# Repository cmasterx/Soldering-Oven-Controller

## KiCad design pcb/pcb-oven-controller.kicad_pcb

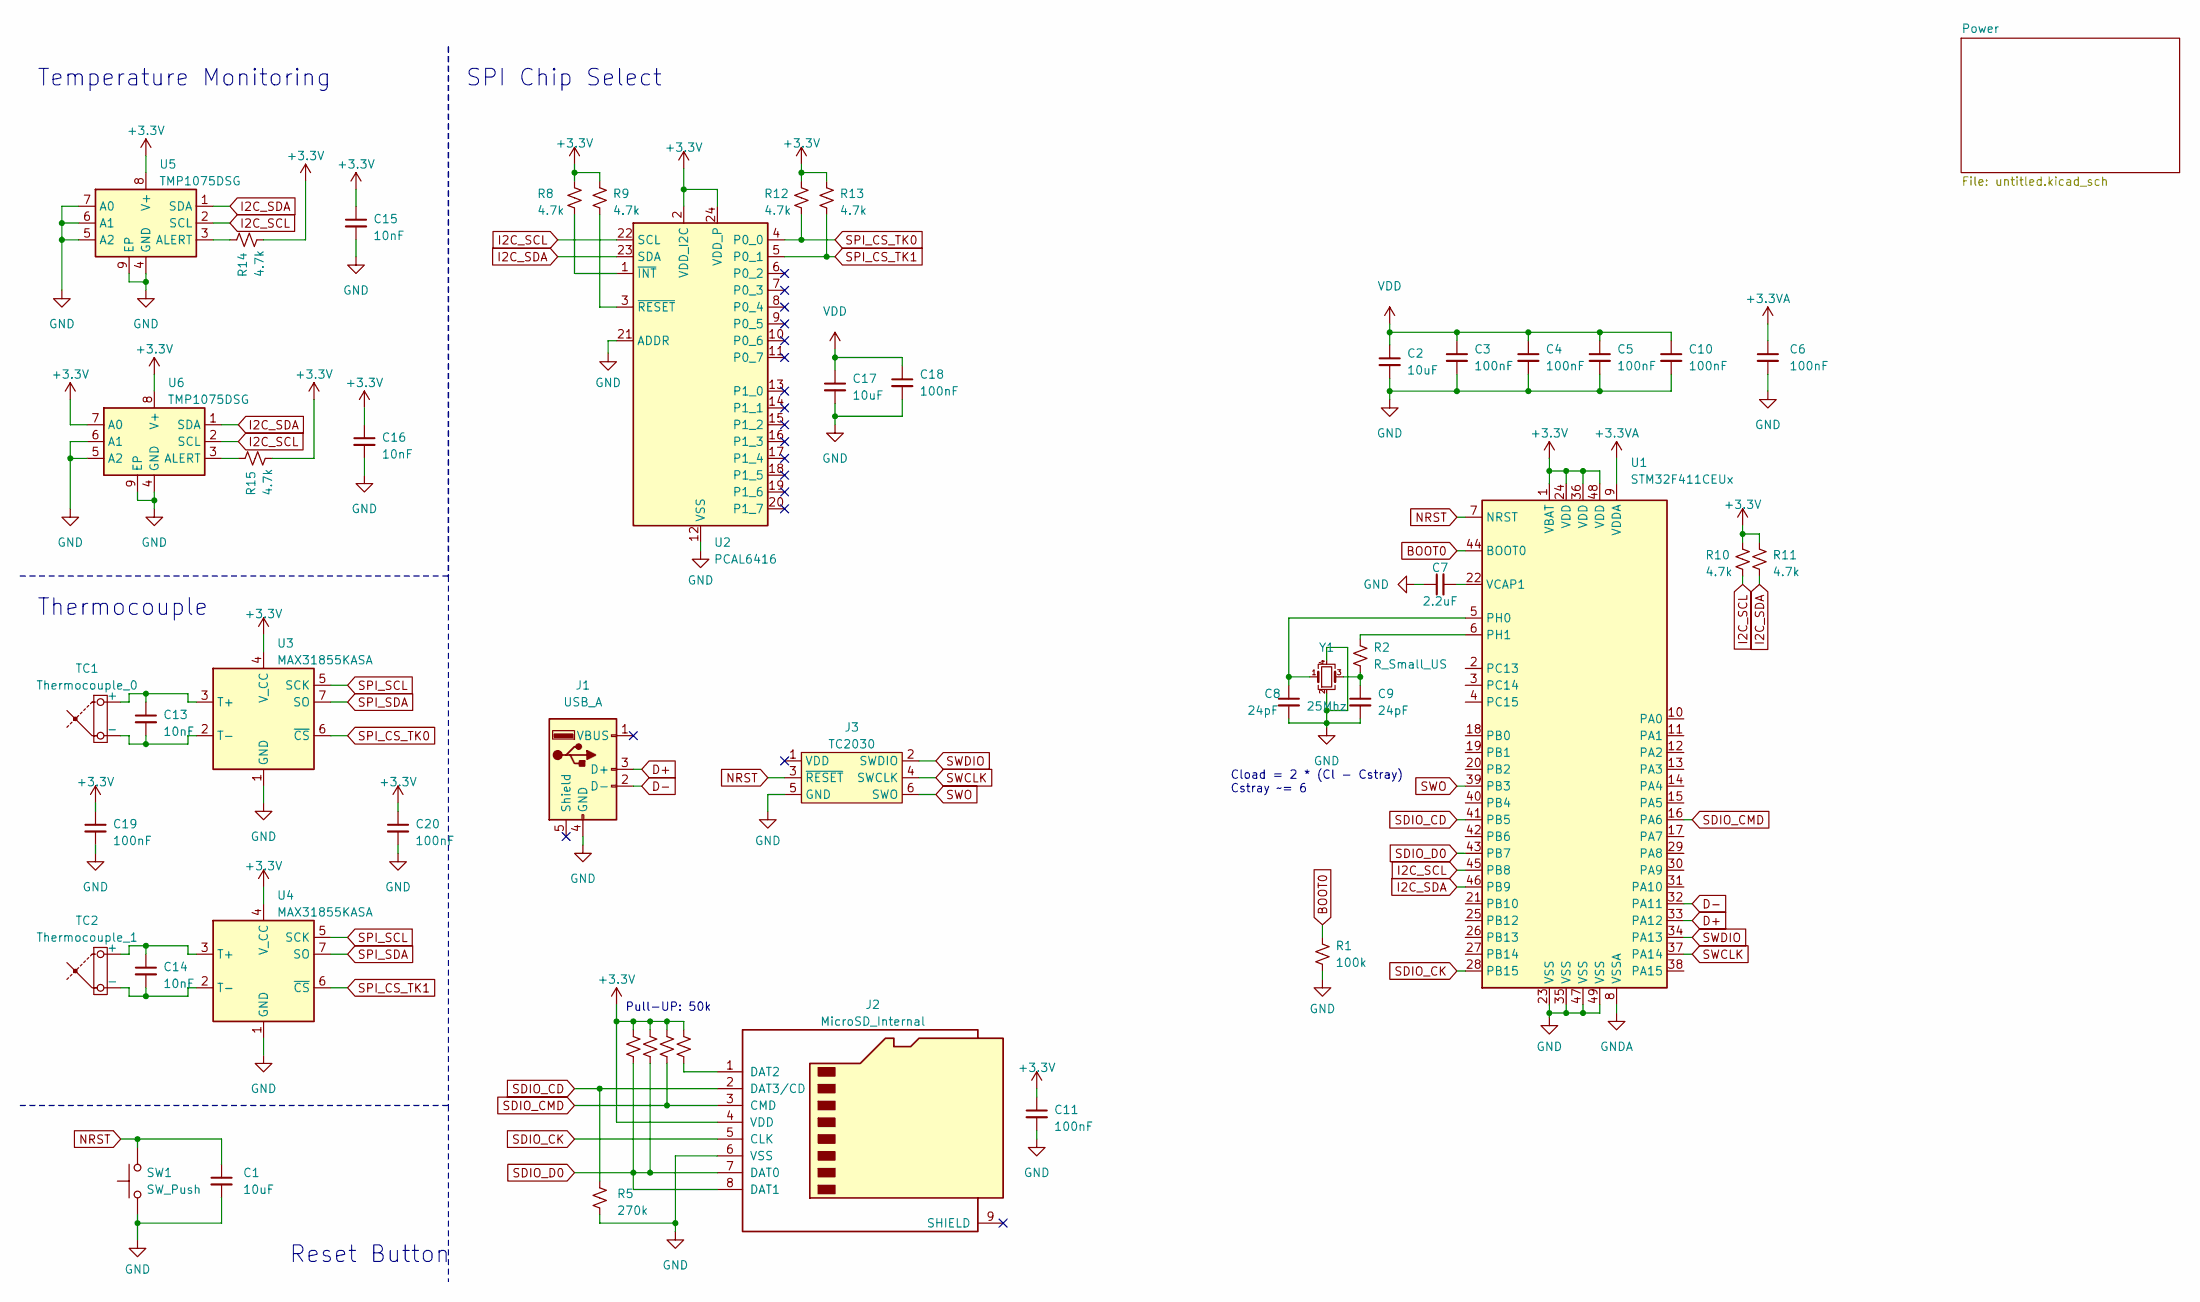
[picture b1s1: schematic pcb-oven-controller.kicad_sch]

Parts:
C1, C2, C17: 10uF; C_0603_1608Metric
C3, C4, C5, C6, C10, C18: 100nF; C_0402_1005Metric
C7: 2.2uF; C_0805_2012Metric
C8, C9: 24pF; C_0402_1005Metric
C11, C19, C20: 100nF; C_0603_1608Metric
C13, C14, C15, C16: 10nF; C_0603_1608Metric
J1: USB_A; USB_A_CNCTech_1001-011-01101_Horizontal
J2: MicroSD_Internal
J3: TC2030; Tag-Connect_TC2030-IDC-NL_2x03_P1.27mm_Vertical
R1: 100k; R_0402_1005Metric
R2: R_Small_US; R_0402_1005Metric
R3, R4, R6, R7: 50k; R_0603_1608Metric
R5: 270k; R_0603_1608Metric
R8, R9, R10, R14, R15: 4.7k; R_0603_1608Metric
R11, R12, R13: 4.7k; R_0603_1608Metric_Pad0.98x0.95mm_HandSolder
SW1: SW_Push; SW_SPST_B3U-1000P
TC1: Thermocouple_0; K_Thermocouple_Generic
TC2: Thermocouple_1; K_Thermocouple_Generic
U1: STM32F411CEUx; QFN-48-1EP_7x7mm_P0.5mm_EP5.6x5.6mm
U2: PCAL6416; WQFN-24-1EP_4x4mm_P0.5mm_EP2.45x2.45mm
U3, U4: MAX31855KASA; SOIC-8_3.9x4.9mm_P1.27mm
U5, U6: TMP1075DSG; WSON-8-1EP_2x2mm_P0.5mm_EP0.9x1.6mm_ThermalVias
Y1: 25Mhz; Crystal_SMD_SeikoEpson_FA238V-4Pin_3.2x2.5mm

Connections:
+3.3V: C11.1, C15.1, C16.1, C19.1, C20.1, J2.4 (VDD), R3.1, R4.1, R6.1, R7.1, R8.1, R9.1, R10.1, R11.1, R12.1, R13.1, R14.2, R15.2, U1.1 (VBAT), U1.24 (VDD), U1.36 (VDD), U1.48 (VDD), U2.2 (VDD_I2C), U2.24 (VDD_P), U3.4 (V_CC), U4.4 (V_CC), U5.8 (V+), U6.7 (A0), U6.8 (V+); also elsewhere on the board
+3.3VA: C6.1, U1.9 (VDDA); also elsewhere on the board
BOOT0: R1.1, U1.44 (BOOT0)
D+: J1.3 (D+), U1.33 (PA12)
D-: J1.2 (D-), U1.32 (PA11)
GND: C1.2, C2.2, C3.2, C4.2, C5.2, C6.2, C7.1, C8.2, C9.2, C10.2, C11.2, C15.2, C16.2, C17.2, C18.2, C19.2, C20.2, J1.4 (GND), J2.6 (VSS), J3.5 (GND), R1.2, R5.2, SW1.1, U1.8 (VSSA), U1.23 (VSS), U1.35 (VSS), U1.47 (VSS), U1.49 (VSS), U2.12 (VSS), U2.21 (ADDR), U3.1 (GND), U4.1 (GND), U5.4 (GND), U5.5 (A2), U5.6 (A1), U5.7 (A0), U5.9 (EP), U6.4 (GND), U6.5 (A2), U6.6 (A1), U6.9 (EP), Y1.2, Y1.4; also elsewhere on the board
I2C_SCL: R10.2, U1.45 (PB8), U2.22 (SCL), U5.2 (SCL), U6.2 (SCL)
I2C_SDA: R11.2, U1.46 (PB9), U2.23 (SDA), U5.1 (SDA), U6.1 (SDA)
NRST: C1.1, J3.3 (~RESET), SW1.2, U1.7 (NRST)
unnamed: C9.1, R2.2, Y1.3
unnamed: J2.1 (DAT2), R3.2
unnamed: C13.1, TC1.1 (+), U3.3 (T+)
unnamed: C13.2, TC1.2 (-), U3.2 (T-)
unnamed: C14.1, TC2.1 (+), U4.3 (T+)
unnamed: C14.2, TC2.2 (-), U4.2 (T-)
unnamed: C8.1, U1.5 (PH0), Y1.1
unnamed: R2.1, U1.6 (PH1)
unnamed: C7.2, U1.22 (VCAP1)
unnamed: R8.2, U2.1 (~INT)
unnamed: R9.2, U2.3 (~RESET)
unnamed: R14.1, U5.3 (ALERT)
unnamed: R15.1, U6.3 (ALERT)
SDIO_CD: J2.2 (DAT3/CD), R5.1, U1.41 (PB5)
SDIO_CK: J2.5 (CLK), U1.28 (PB15)
SDIO_CMD: J2.3 (CMD), R4.2, U1.16 (PA6)
SDIO_D0: J2.7 (DAT0), J2.8 (DAT1), R6.2, R7.2, U1.43 (PB7)
SPI_CS_TK0: R12.2, U2.4 (P0_0), U3.6 (~CS)
SPI_CS_TK1: R13.2, U2.5 (P0_1), U4.6 (~CS)
SPI_SCL: U3.5 (SCK), U4.5 (SCK)
SPI_SDA: U3.7 (SO), U4.7 (SO)
SWCLK: J3.4 (SWCLK), U1.37 (PA14)
SWDIO: J3.2 (SWDIO), U1.34 (PA13)
SWO: J3.6 (SWO), U1.39 (PB3)
VDD: C2.1, C3.1, C4.1, C5.1, C10.1, C17.1, C18.1

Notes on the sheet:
SPI Chip Select
Reset Button
Thermocouple
Pull-UP: 50k
Cload = 2 * (Cl - Cstray) Cstray ~= 6
Temperature Monitoring

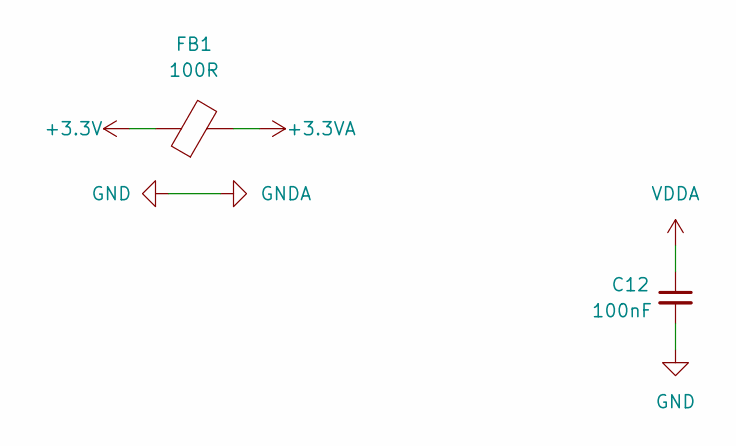
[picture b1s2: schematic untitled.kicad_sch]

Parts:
C12: 100nF; C_0402_1005Metric
FB1: 100R; L_0603_1608Metric

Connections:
+3.3V: FB1.1; also elsewhere on the board
+3.3VA: FB1.2; also elsewhere on the board
GND: C12.2; also elsewhere on the board
VDDA: C12.1; also elsewhere on the board

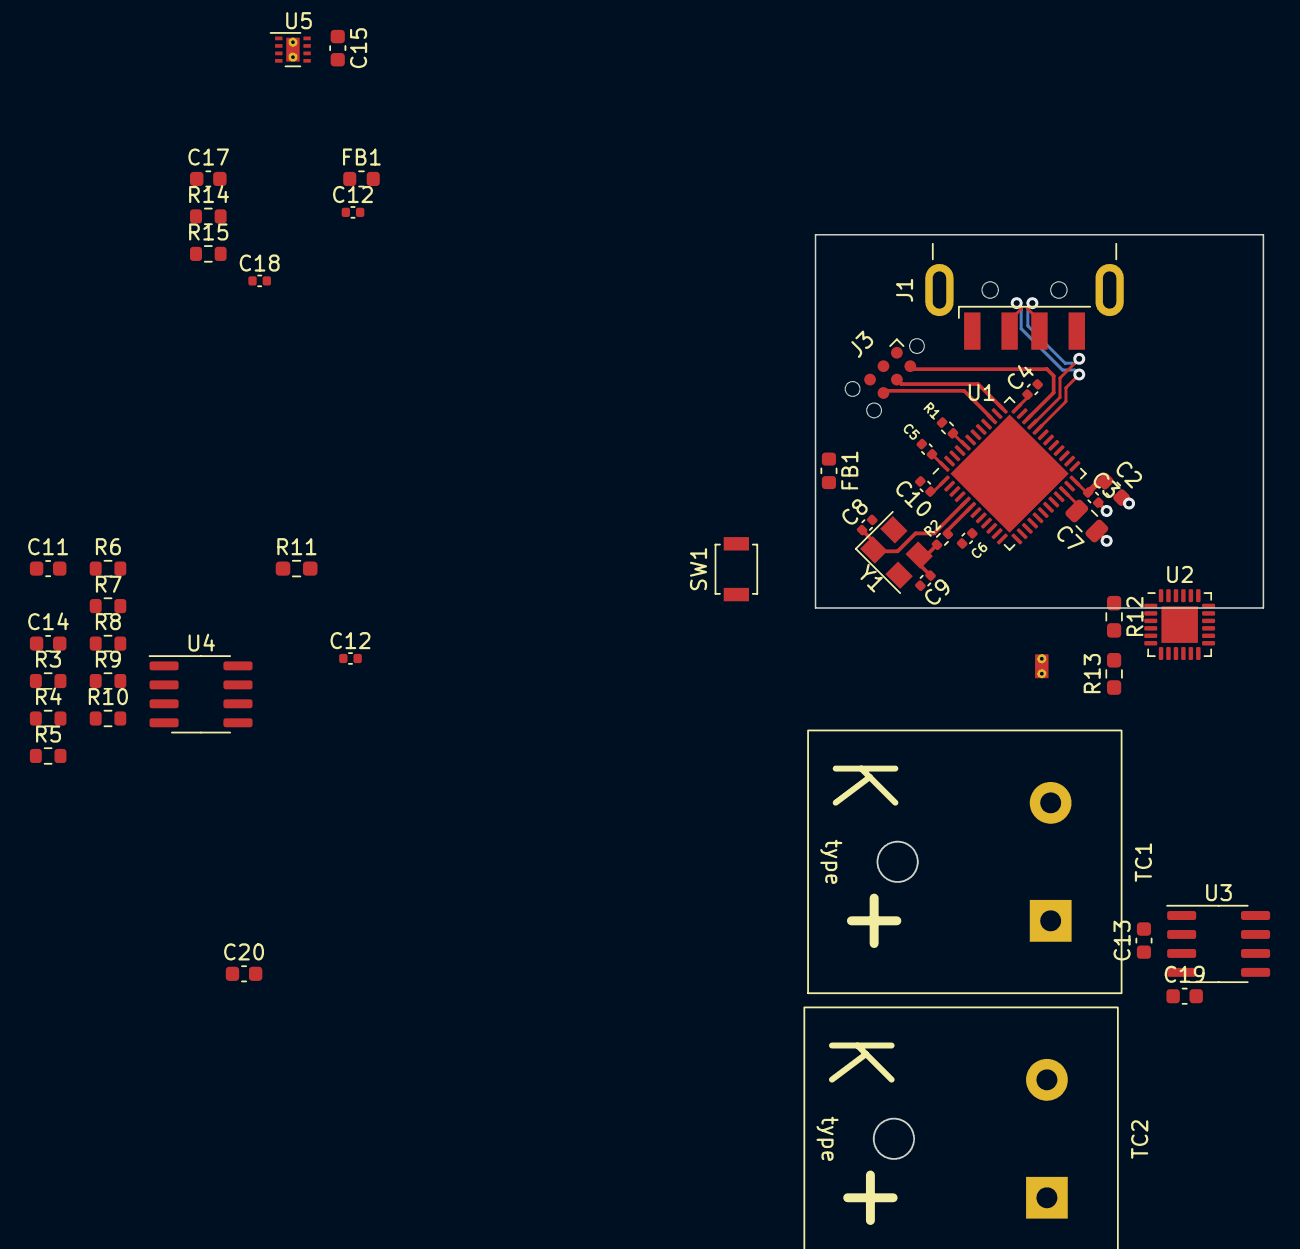
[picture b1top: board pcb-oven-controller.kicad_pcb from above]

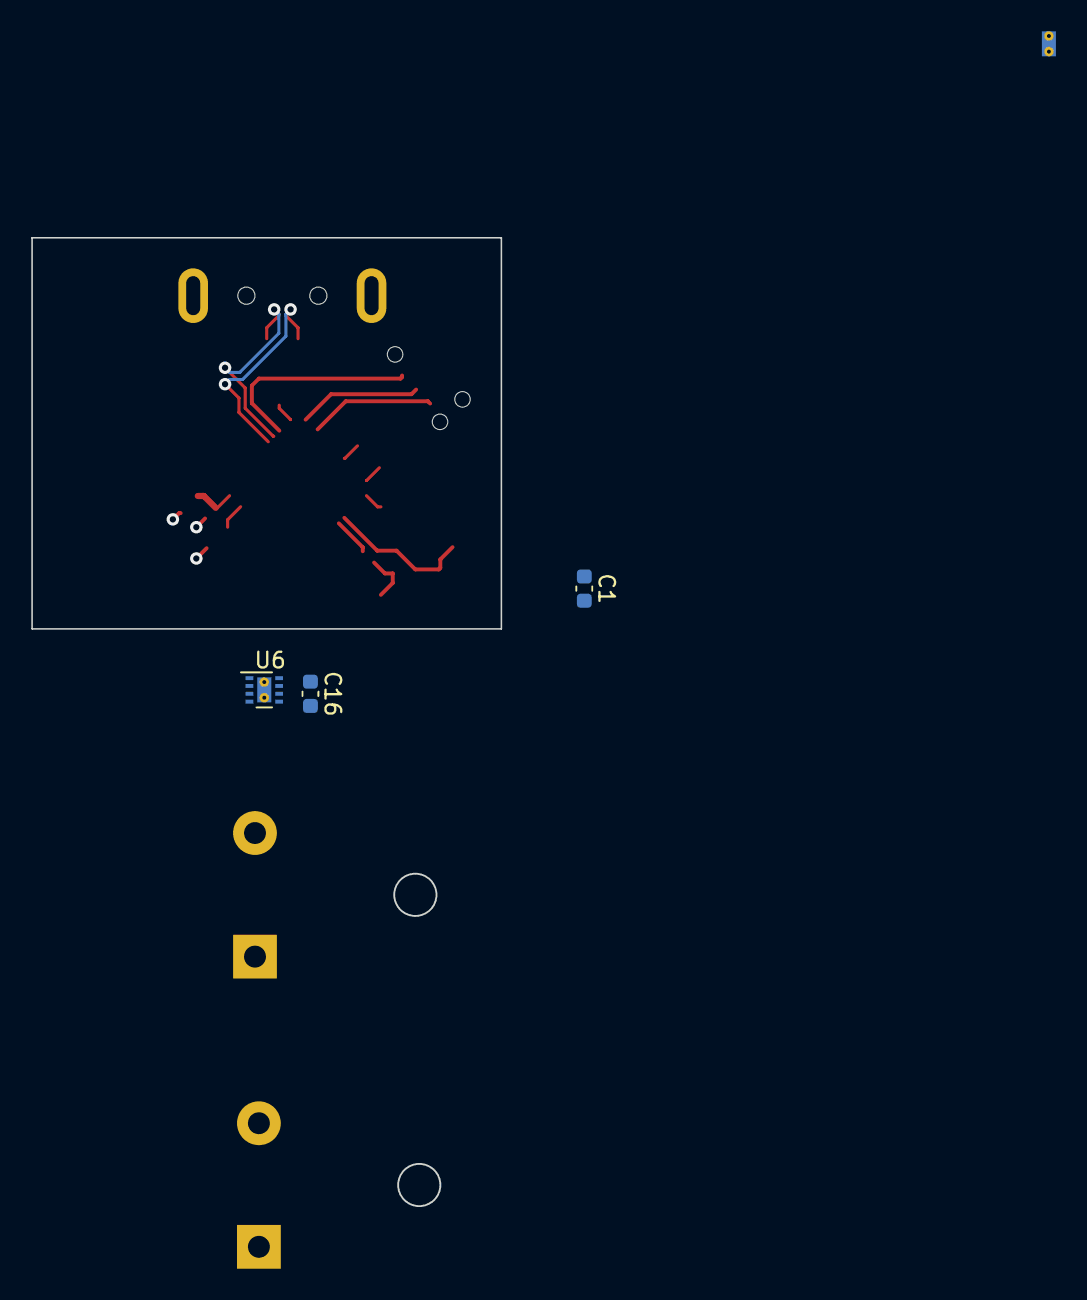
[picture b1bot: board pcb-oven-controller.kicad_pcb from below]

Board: 4 copper layers, 50 parts (3 on the bottom side), 33 nets.

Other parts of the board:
C12#2: 100nF; C_0402_1005Metric
FB1#2: 100R; L_0603_1608Metric

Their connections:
+3.3V: FB1#2.1; also elsewhere on the board
+3.3VA: FB1#2.2; also elsewhere on the board
GND: C12#2.2; also elsewhere on the board
VDDA: C12#2.1; also elsewhere on the board

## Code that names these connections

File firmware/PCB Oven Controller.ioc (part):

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Mcu.Name=STM32F411C(C-E)Ux
Mcu.Package=UFQFPN48
Mcu.UserName=STM32F411CEUx
PA10.GPIOParameters=GPIO_Label
PA10.GPIO_Label=RX
PA10.Mode=Asynchronous
PA10.Signal=USART1_RX
PA11.GPIOParameters=GPIO_Label
PA11.GPIO_Label=USB_DM
PA11.Mode=Host_Only
PA11.Signal=USB_OTG_FS_DM
PA12.GPIOParameters=GPIO_Label
PA12.GPIO_Label=USB_DP
PA12.Mode=Host_Only
PA12.Signal=USB_OTG_FS_DP
PA13.GPIOParameters=GPIO_Label
PA13.GPIO_Label=SWDIO
PA13.Mode=Trace_Asynchronous_SW
PA13.Signal=SYS_JTMS-SWDIO
PA14.GPIOParameters=GPIO_Label
PA14.GPIO_Label=SWCLK
PA14.Mode=Trace_Asynchronous_SW
PA14.Signal=SYS_JTCK-SWCLK
PA15.GPIOParameters=GPIO_Label
PA15.GPIO_Label=PWM0
PA15.Signal=S_TIM2_CH1_ETR
PA2.GPIOParameters=GPIO_Label
PA2.GPIO_Label=UART2_TX
PA2.Mode=Asynchronous
PA2.Signal=USART2_TX
PA3.Mode=Asynchronous
PA3.Signal=USART2_RX
PA5.GPIOParameters=GPIO_Label
PA5.GPIO_Label=SPI_SCK
PA5.Mode=Full_Duplex_Master
PA5.Signal=SPI1_SCK
PA6.Mode=SD_1_bit
PA6.Signal=SDIO_CMD
PA7.GPIOParameters=GPIO_Label
PA7.GPIO_Label=SPI_MOSI
PA7.Mode=Full_Duplex_Master
PA7.Signal=SPI1_MOSI
PA8.Mode=I2C
PA8.Signal=I2C3_SCL
PA9.Mode=Asynchronous
PA9.Signal=USART1_TX
PB0.GPIOParameters=GPIO_Label
PB0.GPIO_Label=DIMMER_SYNC
PB0.Signal=S_TIM3_CH3
PB1.GPIOParameters=GPIO_Label
PB1.GPIO_Label=DRIVE_VBUS_FS
PB1.Signal=GPIO_Output
PB10.GPIOParameters=GPIO_Label
PB10.GPIO_Label=PWM1
PB10.Signal=S_TIM2_CH3
PB12.GPIOParameters=GPIO_Label
PB12.GPIO_Label=SPI_CS2
PB12.Signal=GPIO_Output
PB13.GPIOParameters=GPIO_Label
PB13.GPIO_Label=SPI_CS1
PB13.Signal=GPIO_Output
PB14.GPIOParameters=GPIO_Label
PB14.GPIO_Label=SPI_CS0
PB14.Signal=GPIO_Output
PB15.Mode=SD_1_bit
PB15.Signal=SDIO_CK
PB3.GPIOParameters=GPIO_Label
PB3.GPIO_Label=SWO
PB3.Mode=Trace_Asynchronous_SW
PB3.Signal=SYS_JTDO-SWO
PB4.GPIOParameters=GPIO_Label
PB4.GPIO_Label=SPI_MISO
PB4.Mode=Full_Duplex_Master
PB4.Signal=SPI1_MISO
PB5.GPIOParameters=GPIO_Label
PB5.GPIO_Label=SDIO_IN
PB5.Signal=GPIO_Input
PB6.Mode=I2C
PB6.Signal=I2C1_SCL
PB7.Mode=SD_1_bit
PB7.Signal=SDIO_D0
PB8.Mode=I2C
PB8.Signal=I2C3_SDA
PB9.Mode=I2C
PB9.Signal=I2C1_SDA
PH0\ -\ OSC_IN.GPIOParameters=GPIO_Label
PH0\ -\ OSC_IN.GPIO_Label=HSE_IN
PH0\ -\ OSC_IN.Mode=HSE-External-Oscillator
PH0\ -\ OSC_IN.Signal=RCC_OSC_IN
PH1\ -\ OSC_OUT.GPIOParameters=GPIO_Label
PH1\ -\ OSC_OUT.GPIO_Label=HSE_OUT
PH1\ -\ OSC_OUT.Mode=HSE-External-Oscillator
PH1\ -\ OSC_OUT.Signal=RCC_OSC_OUT
RCC.HSE_VALUE=25000000
RCC.SYSCLKFreq_VALUE=96000000
RCC.SYSCLKSource=RCC_SYSCLKSOURCE_PLLCLK
board=custom

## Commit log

2022-04-26 Initial commit with wip firmware and pcb
2022-04-26 Remove pcb backup files and add pcb backup files to .gitignore
2022-04-26 Add ATL library to proejct
2023-01-26 PCB and firmware changes
2023-01-26 Update ignore files
2023-07-16 Add MicroSD, digital I/O expander, and initial thermocouple IC
2023-09-16 Add more pcb progress
2023-09-16 Update KiCAD ATL lib
2023-09-16 Add firmware files
2023-12-25 Update .gitignore to ignore lock files and .DS_Store files
